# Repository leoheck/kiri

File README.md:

# KiCad Revision Inspector (KiRI)

KiRI started as a script to experiment having a visual diff tool for KiCad projects including schematics and layouts.
After some time, it became an interesting and it is still being updated.

Currently, KiRi supports KiCad >= 5.

Internally it uses existing tools to generate svg images of schematics and layouts to be compared.

In this way, when exporting schematics, if:

- KiCad >= 7 is installed, the `kicad-cli` is used.
- KiCad 6 is installed (which does not have `kicad-cli` available), schematics are exported using [xdotool](https://github.com/jordansissel/xdotool) on Linux/Windows and [cliclick](https://github.com/BlueM/cliclick) on macOS, using the GUI. This method is far from the ideal and it is not recommended.
- KiCad 5 is installed or if the projects is based on KiCad 5, [plotkicadsch/plotgitsch](https://github.com/jnavila/plotkicadsch) are used to export the schematics.

However, when exporting the layout layers:

- [Kicad-Diff](https://github.com/Gasman2014/KiCad-Diff) is used for all supported KiCad versions using `pcbnew` library available in python. It is also possible to use `kicad-cli` to export the layout layers however this process is slower than using Kicad-Diff since the other exports all the layers at once and `kicad-cli` can only do one layer at a time.

## KiRI Installation

Check the Installation instructions, [here](INSTALL.md).

## Using KiRI

KiRI can be launched with the following command, anywhere, inside or outside of the repository of the project.

```bash
kiri [OPTIONS] [KICAD_PROJECT_FILE]
```

`KICAD_PROJECT_FILE` can be passed, but it can also be omitted. If running from inside the project's repository, it will use the `.pro` or `.kicad_pro` available. If both are present (which is not good), it will ask your choice. The same happens is running outside of the repository without passing the `KICAD_PROJECT_FILE`.

## Command line options (aka Help)

Command line flags can be seen using the `-h` flag
```bash
kiri -h
```

### Archiving generated files

There is a possibility to archive generated files (check the help above).

To visualize generated files it is not necessary to have KiRI installed. You just have to unpack the generated package and then execute the web-server script (`./kiri-server`) inside of the folder, as shown below:

```bash
tar -xvzf kiri-2021.11.18-16h39.tgz
cd kiri
./kiri-server .
```

# KiCad Integration

It is possible to integrate KiRI with PCBNew by adding a button to its toolbar with the following command:

```bash
# Create folder if it does not exist
mkdir -p "~/.kicad/scripting/plugins"

# Copy the plugin there
cd ./kiri
cp -r "./kicad/plugin/kiri_v6/" "~/.kicad/scripting/plugins/kiri"
```

# KiRI Screenshots

Browsing the schematic view walking through and comparing each page of the schematics, individually.

Browsing the layout view walking through and comparing each layer of the layout, individually.

Here is the comparison of the schematics when the project is updated from using KiCad 5 (`.sch`) to KiCad 6 (`.kicad_sch`).

Shortcuts are a really good way of walking through the commits, pages and layers quickly. Check the available shortcuts by hitting the shortcut `i`.

A quick and old demo on the Youtube.

<p align="center">

</p>

---

<p align="center">
Are you enjoying using this tool, feel free to pay me a beer :). Cheers!
</p>

<p align="center">
    
</p>

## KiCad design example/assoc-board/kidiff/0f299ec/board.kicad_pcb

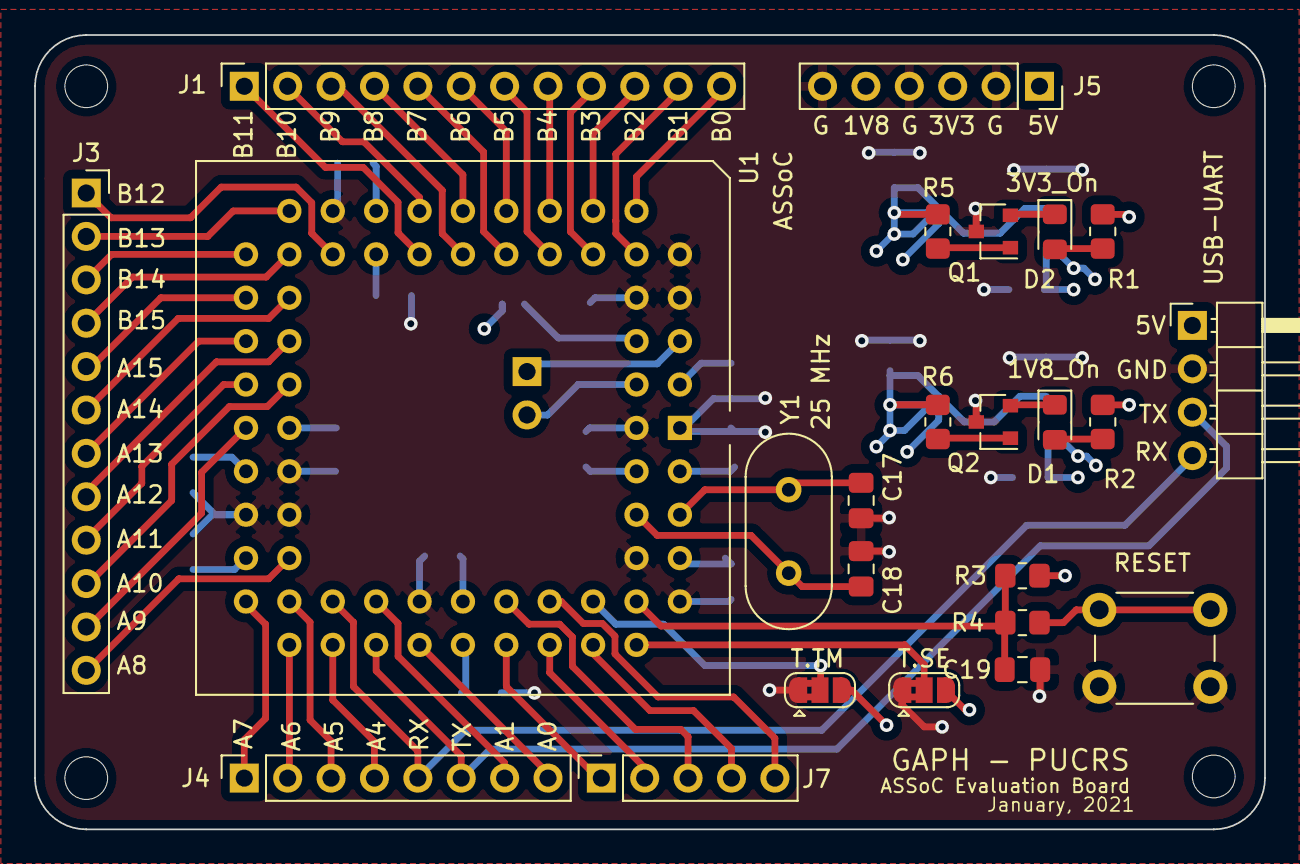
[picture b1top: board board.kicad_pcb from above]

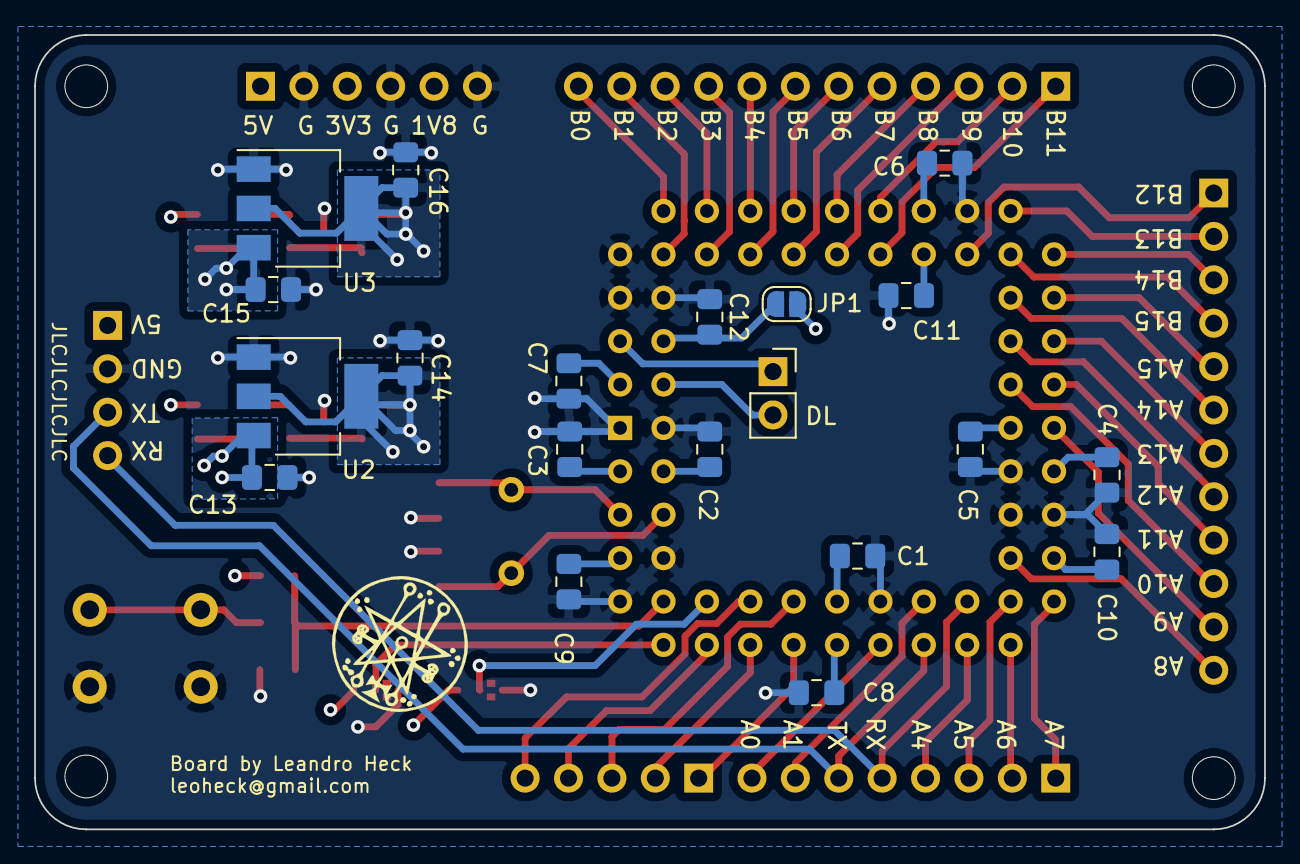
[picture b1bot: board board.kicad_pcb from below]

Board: 4 copper layers, 72.0 x 46.5 mm, 48 parts (20 on the bottom side), 56 nets.

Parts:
C1, C2, C3, C4, C5, C6, C7, C8, C9, C10, C11, C12, C19: 100n; C_0805_2012Metric_Pad1.18x1.45mm_HandSolder
C13, C14, C15, C16: 10u; C_0805_2012Metric_Pad1.18x1.45mm_HandSolder
C17: 18p; C_0805_2012Metric_Pad1.18x1.45mm_HandSolder
C18: 18n; C_0805_2012Metric_Pad1.18x1.45mm_HandSolder
D1: 1V8_On; LED_0805_2012Metric_Pad1.15x1.40mm_HandSolder
D2: 3V3_On; LED_0805_2012Metric_Pad1.15x1.40mm_HandSolder
H1, H2, H3, H4: MountingHole; MountingHole_2.5mm
J1: H3; PinSocket_1x12_P2.54mm_Vertical
J2: USB-UART; PinHeader_1x04_P2.54mm_Horizontal
J3: H2; PinSocket_1x12_P2.54mm_Vertical
J4: H1; PinSocket_1x08_P2.54mm_Vertical
J5: PWR; PinSocket_1x06_P2.54mm_Vertical
J6: DL; PinSocket_1x02_P2.54mm_Vertical
J7: H4; PinSocket_1x05_P2.54mm_Vertical
JP1: SolderJumper_2_Bridged; SolderJumper-2_P1.3mm_Open_RoundedPad1.0x1.5mm
JP2: T.SE; SolderJumper-3_P1.3mm_Bridged2Bar12_RoundedPad1.0x1.5mm
JP3: T.TM; SolderJumper-3_P1.3mm_Bridged2Bar12_RoundedPad1.0x1.5mm
Q1, Q2: Q_NPN_BCE; SOT-23
R1, R2: 330; R_0805_2012Metric_Pad1.20x1.40mm_HandSolder
R3: 10K; R_0805_2012Metric_Pad1.20x1.40mm_HandSolder
R4: 1K; R_0805_2012Metric_Pad1.20x1.40mm_HandSolder
R5, R6: 1k; R_0805_2012Metric_Pad1.20x1.40mm_HandSolder
SW1: RESET; SW_PUSH_6mm
U1: ASSoC; PLCC-68_THT-Socket
U2, U3: LM1117-3.3; SOT-223
Y1: 25 MHz; Crystal_HC49-4H_Vertical

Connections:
+1V8: C8.1, C9.1, C10.1, C11.1, C14.1, J5.3, JP1.2, R6.2, U1.23, U1.41, U1.52, U1.63, U2.2
+3V3: C1.1, C2.1, C3.1, C4.1, C5.1, C6.1, C7.1, C16.1, J5.5, JP2.3, JP3.3, R3.1, R5.2, U1.3, U1.22, U1.36, U1.37, U1.53, U1.67, U1.68, U3.2
+5V: C13.1, C15.1, J2.1, J5.1, R1.1, R2.1, U2.3, U3.3
/1V8_ASYNC: C12.1, JP1.1, U1.6
/A0: J4.8, U1.50
/A1: J4.7, U1.49
/A4: J4.4, U1.46
/A5: J4.3, U1.45
/A6: J4.2, U1.44
/A7: J4.1, U1.43
/A8: J3.12, U1.42
/A9: J3.11, U1.35
/A10: J3.10, U1.34
/A11: J3.9, U1.33
/A12: J3.8, U1.32
/A13: J3.7, U1.31
/A14: J3.6, U1.30
/A15: J3.5, U1.29
/ASSOC_RST: C19.2, R3.2, R4.1, U1.62
/ASSOC_RX: J2.4, J4.5, U1.47
/ASSOC_TX: J2.3, J4.6, U1.48
/B0: J1.12, U1.10
/B1: J1.11, U1.11
/B2: J1.10, U1.12
/B3: J1.9, U1.13
/B4: J1.8, U1.14
/B5: J1.7, U1.15
/B6: J1.6, U1.16
/B7: J1.5, U1.17
/B8: J1.4, U1.18
/B9: J1.3, U1.19
/B10: J1.2, U1.20
/B11: J1.1, U1.21
/B12: J3.4, U1.28
/B13: J3.3, U1.27
/B14: J3.2, U1.26
/B15: J3.1, U1.25
/DL_I: J6.2, U1.4
/DL_O: J6.1, U1.5
/M.MISO: J7.1, U1.54
/M.MOSI: J7.3, U1.55
/M.SCLK: J7.2, U1.56
/M.SS.RAM: J7.5, U1.57
/M.SS.ROM: J7.4, U1.58
/TEST.SE: JP2.2, U1.60
/TEST.TM: JP3.2, U1.59
/XI: C17.2, U1.65, Y1.2
/XO: C18.2, U1.66, Y1.1
GND: C1.2, C2.2, C3.2, C4.2, C5.2, C6.2, C7.2, C8.2, C9.2, C10.2, C11.2, C12.2, C13.2, C14.2, C15.2, C16.2, C17.1, C18.1, C19.1, J2.2, J5.2, J5.4, J5.6, JP2.1, JP3.1, Q1.3, Q2.3, SW1.1, U1.1, U1.2, U1.7, U1.8, U1.9, U1.24, U1.38, U1.39, U1.40, U1.51, U1.61, U1.64, U2.1, U3.1
unnamed: D1.1, Q2.2
unnamed: D1.2, R2.2
unnamed: D2.1, Q1.2
unnamed: D2.2, R1.2
unnamed: Q1.1, R5.1
unnamed: Q2.1, R6.1
unnamed: R4.2, SW1.2

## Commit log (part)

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2022-07-12 Improve commits table tooltips
2022-07-12 Fix terminal output
2022-07-12 Minor improvements
2022-07-12 Check if project is a git repository
2022-07-12 Simplify export_project_files by exporting everything from each revision
2022-07-12 Improve detection of hierarchical sheets on Kicad 6 projects
2022-07-12 Improve svg naming
2022-07-12 Support multi-nested pages on Kicad 5 too
2022-07-12 Improving script
2022-07-12 Update script name
2022-07-12 Improve script
2022-07-12 Change variable
2022-07-13 Revert issue with commits
2022-07-13 Change submodule url
2022-07-13 Update submodule
2022-07-13 Add extra module path
2022-07-13 Remove unused python dependency
2022-07-13 Update to restore user keyboard
2022-07-13 Improve WLS info
2022-07-13 Dissmiss initial windows if kicad was never launched
2022-07-13 Improve info
2022-07-13 Remove duplicated info
2022-07-13 Stop adding extra images
2022-07-13 Initial support for launching Kicad in the current Rev
2022-07-13 Update libs and scripts
2022-07-13 Revert font-awesome.min.css version
2022-07-13 Improve commit label to make things static
2022-07-13 Initial links customization
2022-07-13 Improve display
2022-07-13 Fix some variables
2022-07-13 Add extra info to set the DISPLAY for Windows users
2022-07-13 Adjust some variable names
2022-07-13 Remove blank line
2022-07-13 Improve multi-nested-pages on macOS too
2022-07-13 Fix path
2022-07-14 Improve tooltips (on Chrome)
2022-07-14 Update link colors
2022-07-14 Initial steps to open Revs with Kicad
2022-07-15 Convert local revision strings to _local_
2022-07-15 Organize generated files related with layout
2022-07-15 Organize pages/layers in sch_sheets/pcb_layers
2022-07-15 Comment WLS special browser to use kiri-server as default
2022-07-15 Organize schematic images
2022-07-15 Improve plot_kicad_sch
2022-07-15 Add rename as dependecny
2022-07-15 Return USER when local commit does not have a User Name
2022-07-24 Remove macOS quarantine and refresh eeschema window
2022-07-24 Fix script name (mostly for macOS)
2022-07-24 Fix sch_sheets path
2022-07-24 Break command to fit GitHub display
2022-07-25 Fix _local_ pcb files
2022-07-25 Update view when page loads
2022-07-25 Remove limitation text
2022-07-26 Improve some tags
2022-07-26 Load sheets and layets dynamically for each commit pair
2022-07-26 Improve schematic discovery for when instance names have spaces
2022-07-26 Natural sort sheet instances
2022-07-26 Remove unecessary / that closes tags
2022-07-26 Minor changes
2022-07-28 Add comment
2022-07-28 Update List of layers/sheets only when needed
2022-07-28 Improve symbols for changed objects on nested projects
2022-08-04 reset keyboard also with xdotool
2022-08-05 Add note regarding version of rename command
2022-08-05 Update ids of new elements
2022-08-05 Remove initial images and update info of shortcuts
2022-08-05 Rewrite svg-pan-zoom. Do not update layers list if not needed. Improve shortcuts adding pan and zoom.
2022-08-05 Change python to python3
2022-08-05 Set max pages/layers list size. Create a new way ot show shortcuts/info. Hide tooltips when commit changes so they wont be stuck
2022-08-07 Atempt to fix blind/burreid vias (takes long time to process)
2022-08-07 Prevent removing svg-pan-zoom when layers/pages change. This preserves zoom level too.
2022-08-07 Preserve zoom/pan when changing view
2022-08-07 Fix holes/vias appearning on all layers
2022-08-08 Fullscreen view
2022-08-08 Add modal view with shortcuts
2022-08-08 Revert up/down pan. Use original Kicad layer names with dot instead of underline
2022-08-09 Fix html tags/properties
2022-08-09 Update output
2022-08-09 Fix buttons that changes the view
2022-08-09 jshint
2022-08-09 Fix focus blur on shortcuts button
2022-09-11 Update OPAM version so it will work on macOS M1 too
2022-09-11 Update Kicad-Diff branch
2022-09-30 Select the first sheet when there is no one selected
2022-09-30 Fix page selection by value when values have spaces (page names with spaces)
2022-09-30 Hide images when there is no kicad_pcb
2022-09-30 Improve behavior when layer names change (quick fix)
2022-10-29 Fix distro indication
2022-10-29 Normalize rename tool for fedora that is using prename instead
2022-11-14 Fix recursion
2022-11-14 Force english to preserve shortcut that depends on alt
2022-11-18 Initialize OPAM inside the function
2022-11-18 Add bc as dependency
2022-11-18 Testing
2022-11-21 Replace apt with apt-get
2022-11-21 Add flag to override ip address
2022-11-21 Add command to override the defaul ip address
2022-12-09 Add reference to Kiri-Docker project
2022-12-12 Add kicad version to the version command
2022-12-13 Improve window management
2022-12-15 Update Kicad-Diff
2022-12-15 Revert hashes to short without forcing them
2022-12-15 Fix padding
2022-12-15 Do not for python packages to upgrade
2022-12-16 Drop single use bc, and score that was not being used
2022-12-16 Remove dune as dependency
2022-12-16 Remove single use of getent
2022-12-16 Fix C.utf8 locale on WSL that uses C.UTF-8 instead
2023-01-19 Improve shortcuts
2023-01-19 Remove whitespace
2023-01-19 Do not cycle the Next/Previows Sch/PCB by default. Combining with the Ctrl key enables this.
2023-02-06 Include others Ubuntu-based (Debian derived) distros like Mint
2023-02-22 Use kicad-cli for schematics instead of xdotool
2023-02-22 Add patsh for macOS
2023-02-22 Update macOS dependencies
2023-02-22 Fix missing function and else statement
2023-03-23 Fix python path for Kicad 7
2023-03-23 Update for Kicad 7
2023-03-26 Update to Kicad 7
2023-03-26 Update text of _local_ commit
2023-03-26 remove old env scripts
2023-03-26 Collect kicad version of each rev
2023-03-26 Change internal folder name
2023-03-26 Update text
2023-03-26 Fix number the number of comparisons and improve info
2023-03-27 Improve syntax
2023-03-27 Fix schematic version
2023-03-27 Fix arguments with spaces
2023-03-27 Fix python cmd for macOS
2023-03-28 Use which silently
2023-03-28 Add install for pacman
2023-03-28 rename is perl-rename on arch/manjaro
2023-03-28 Improve text
2023-03-28 Fix inverted logic for checking if DISPLAY set
    I think `-n` and `-z` were mixed up here. The previous code overwrote the `DISPLAY` variable if it's already set. This update only sets a default value if `DISPLAY` is NOT already set.
    From `man test`:
    ```
    -n STRING
    the length of STRING is nonzero
    -z STRING
2023-03-28 Find KIRI_HOME_PATH even if $0 is symlink
    If `kiri` is run via a symlink, then `KIRI_HOME_PATH` will point to the directory of the symlink, not the true kiri home directory.
2023-03-28 Fix pamac vs. pacman
    `pamac` is not available on stock Arch Linux. All of these packages can be installed with `pacman`. Also, there's no need for `-Suy` every time. That would be the equivalent of `sudo apt update && su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
2023-03-28 Say yes to all while installing with pacman
2023-03-29 Fix null terminated strings one WSL/Windows
2023-03-29 Update images
2023-03-29 New image
2023-03-29 Add installation in another file
2023-03-30 Paypal donation
2023-03-30 Add donation button
2023-03-30 Remove unecessary comments
2023-03-30 Fix filenames of artifacts
    kicad-cli exports artifacts using the sheet title, not the sheet file name. Use the `sch_sheets`
    file to rename the files back to how the frontend expects
2023-03-30 Only rename files if actually different
    Prevents `mv: 'filename' and 'filename' are the same file`
2023-03-31 Improve info when viewing on fullscreen
2023-03-31 Fix tooltip data-toggle
2023-03-31 Improve tooltip bondary
2023-03-31 Update tooltop of pages
2023-04-01 Fix local rev folder name
2023-04-01 Remove duplicated page of extra pages info and skip when there is no project file
2023-04-01 Fix rev kicad project path
2023-04-01 Update tooltips
2023-04-04 Add Python requirements.txt
2023-04-05 Remove `readonly` from PAGES_FILE_X
2023-04-06 Revert previows behavior of the project selector
2023-04-12 Remove GUI selector of the .kicad_pro
2023-04-12 Improve the local changes detection for nested projects
2023-04-12 Fix syntax of variables
2023-04-12 Fix the missing part of Marcel Robitaille work
2023-05-17 Improve Kicad-Diff error messages
2023-05-29 Fix SetSvgPrecision command on Kicad 7.0.5
2023-05-29 When using verbose, show the error output
2023-06-03 kiri: Add --no-error-on-commit-count
2023-06-03 kiri.js: Load favicon.ico at a relative path
    This fixes the server status when files are served from a subdirectory
2023-06-04 Having less than 2 commits is not an error
2023-07-25 Improve manual commits selection
2023-07-25 Add a way to compare between branches
2023-07-29 Fix commit label when plotting schematics
2023-07-31 Fix xargs missing on macos
2023-08-05 Fix shortcut for the info button
2023-08-05 Disable 3d generation
2023-08-05 Address the issue where the page does not change when clicking in the list
2023-08-05 Fix comment
2023-08-05 Ignore tests, and filter svg files
2023-08-05 Add flag to force using kicad-cli to plot layout (slow)
2023-08-10 layout file rename explicitly matches final project_name string with digits
2023-08-11 Improve format
2023-08-24 Update to install the plugin for Kicad >= 6
2023-08-25 Toogle old/new visibility with shortcuts q/w
2023-08-25 Improve visibility of commits when switching to fullscreen
2023-08-26 Keep commits visibility when changing view
2023-08-26 Change image color to white when viweing it solo
2023-08-28 Add workaround to set the xy of the viewbox of the SVG files
2023-08-28 Typo
2023-08-29 Keep hidden commit when changing view and also fix when toggling it with the other shortcut
2023-08-30 add support for Asahi Linux
2023-08-30 Fix fulscreen when switching view and improve legend colors
2023-09-06 Fix zoom that was broken
2023-09-29 Provide a path to python-requirements.txt when installing Python dependencies
2023-11-28 Restore the original keyboard layout when the script is killed
2023-11-29 Restore keyboard when the script fails
2023-11-29 Optimize svgs and remove dos2unix
2023-11-29 Remove dos2unix
2023-11-29 Increase zoomScaleSensitivity
2023-11-29 Fix kiri path
2023-11-29 Update format
2023-11-29 Add option to compare 2 specific commits like git does
2023-11-29 Add some parenthesis
2023-12-01 List of pages/layers are generared on the fly
2023-12-05 Comment out layers comparison (slow and not efficient)
2024-01-03 Backport of KiBot's KiRi integration
    - The only missing part is embedding the CSS, JS and SVG icons
    But the result is functional
2024-02-28 fix plot_kicad_sch and kiri
    * fix launch_eeschema() when there are more locales available
    * remove exit 1 in get_git_commits_list() to retrieve list of commits
2024-03-01 add support for git tags
2024-04-04 Add flag to exclude kicad project files with a pattern
2024-04-04 Improve version
2024-04-04 Improve sch/pcb kicad version parsing
2024-04-04 Improve sch/pcb page data parsing
2024-04-04 Fix date on MacOS
2024-04-05 Fix date for version on MacOS
2024-04-05 Improve behavior on MacOS
2024-04-05 Fix pcb version selector
2024-04-05 Improve language selector
2024-04-05 Improve pontual HASH/TAG comparisons
2024-04-16 Improve behavior when files have spaces
2024-04-16 Fix layer names when parsing Kicad 8 pcb
2024-04-16 Update pcbnew path for Kicad 8 on linux
2024-05-20 Fix commits selector
2024-05-28 Fix CRLF line ending on _local_ files (problem mostly happen when using git on windows)
2024-05-28 Use a better way to locate files with CRLF line endigns and convert to linux format
2024-05-28 Minor text output update
2024-11-06 Update plugin msg
2024-11-06 Update plugin install msg
2024-11-06 Fix -u flag
2024-11-06 Improve plugin execution
2024-12-06 Add support for git lfs files
    When kicad files are stored in a git repo as lfs files
    'git archive' command stores only pointers. 'git archive'
    can't handle lfs files so after they are stored they need to be
    processed by 'git lfs smudge' command to get actual files.
2024-12-10 Update variable style
2025-01-29 Improve commits filter
2025-01-30 Improve flags name for selecting newest/oldest commits
2025-01-30 Fix messages and the help
2025-01-30 Fix command to list commits
2025-03-04 Fix for when boards have points in the filename
2025-03-05 Added missing MacOS M1 dependencies
2025-03-12 Improve project name selection when having multiples projects in the same folder
2025-04-02 Ignore removed command (on Kicad 9.0.1)
2026-03-08 Improve kicad version parsing
